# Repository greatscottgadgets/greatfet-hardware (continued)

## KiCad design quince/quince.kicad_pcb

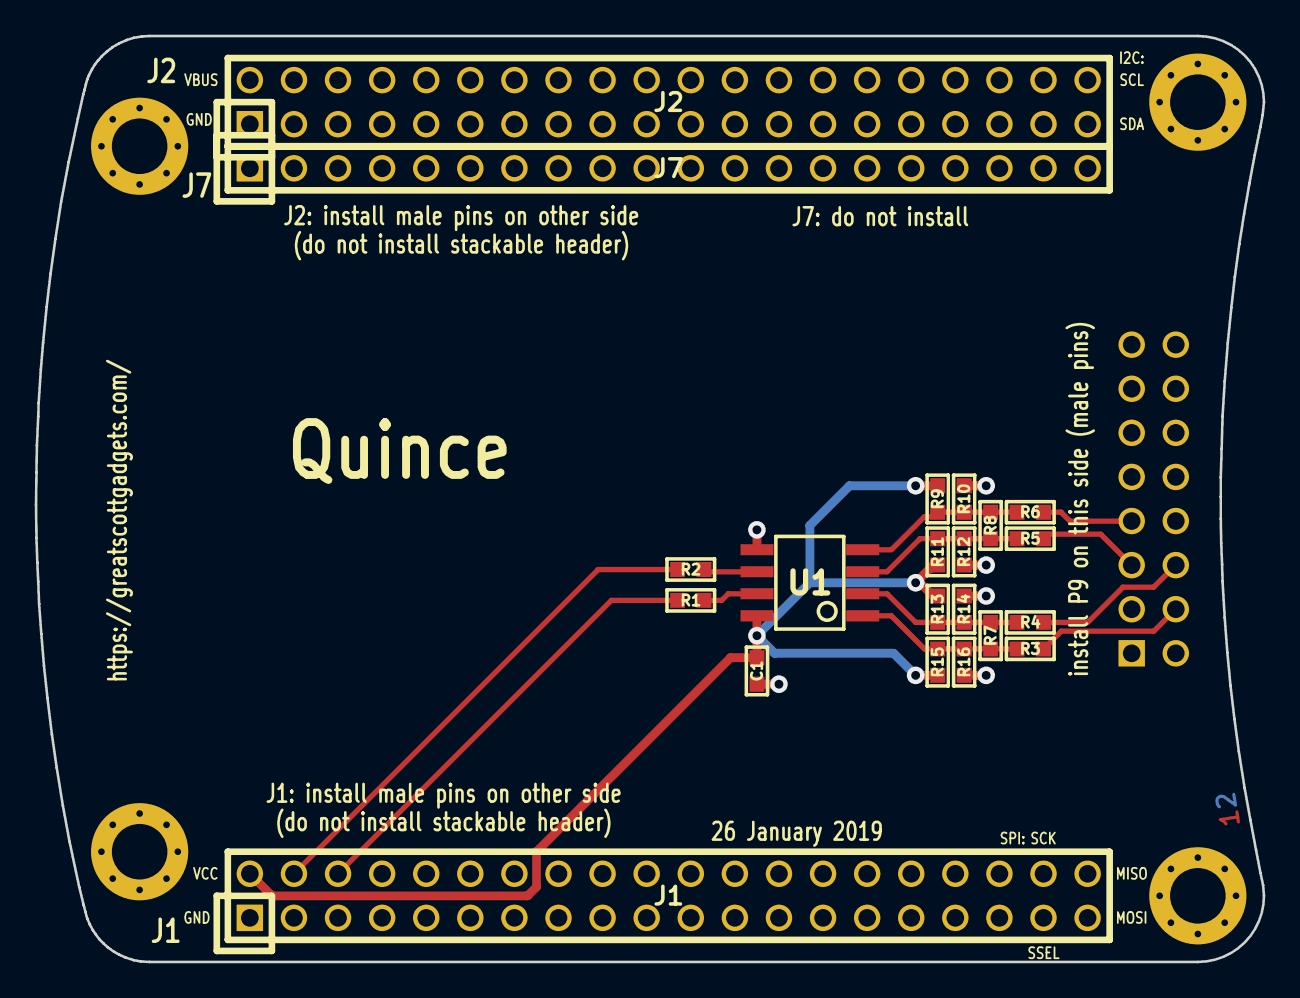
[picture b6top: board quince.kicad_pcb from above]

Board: 2 copper layers, 70.7 x 53.3 mm, 26 parts (1 on the bottom side), 14 nets.

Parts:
C1: C; 0603
J1: NEIGHBOR1; HEADER-2x20
J2: NEIGHBOR2; HEADER-2x20
J7: BONUS_ROW; HEADER-1x20
MH1, MH2, MH3, MH4: MOUNTING_HOLE; HOLE126MIL-COPPER
P9: BASEBAND; HEADER-2x8
R1, R2, R3, R4, R5, R6: 0; 0603
R7, R8, R9, R10, R11, R12, R13, R14, R15, R16: R; 0603
U1: TLV3502; SOIC8-154

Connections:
/+IN_A: R3.1, R7.1, R15.2, R16.1, U1.1
/+IN_B: R5.1, R8.1, R11.2, R12.1, U1.3
/-IN_A: R4.1, R7.2, R13.2, R14.1, U1.2
/-IN_B: R6.1, R8.2, R9.2, R10.1, U1.4
/OUT_A: R1.2, U1.7
/OUT_B: R2.2, U1.6
/P0_0: J1.4, R2.1
/P0_1: J1.6, R1.1
/RXBBI+: P9.7, R6.2
/RXBBI-: P9.5, R5.2
/RXBBQ+: P9.6, R4.2
/RXBBQ-: P9.4, R3.2
GND: C1.1, J1.1, J2.1, J7.1, J7.10, J7.19, MH1.1, MH2.1, MH3.1, MH4.1, P9.1, P9.2, P9.3, P9.8, P9.9, P9.14, P9.15, P9.16, R10.2, R12.2, R14.2, R16.2, U1.5
VCC: C1.2, J1.2, R9.1, R11.1, R13.1, R15.1, U1.8

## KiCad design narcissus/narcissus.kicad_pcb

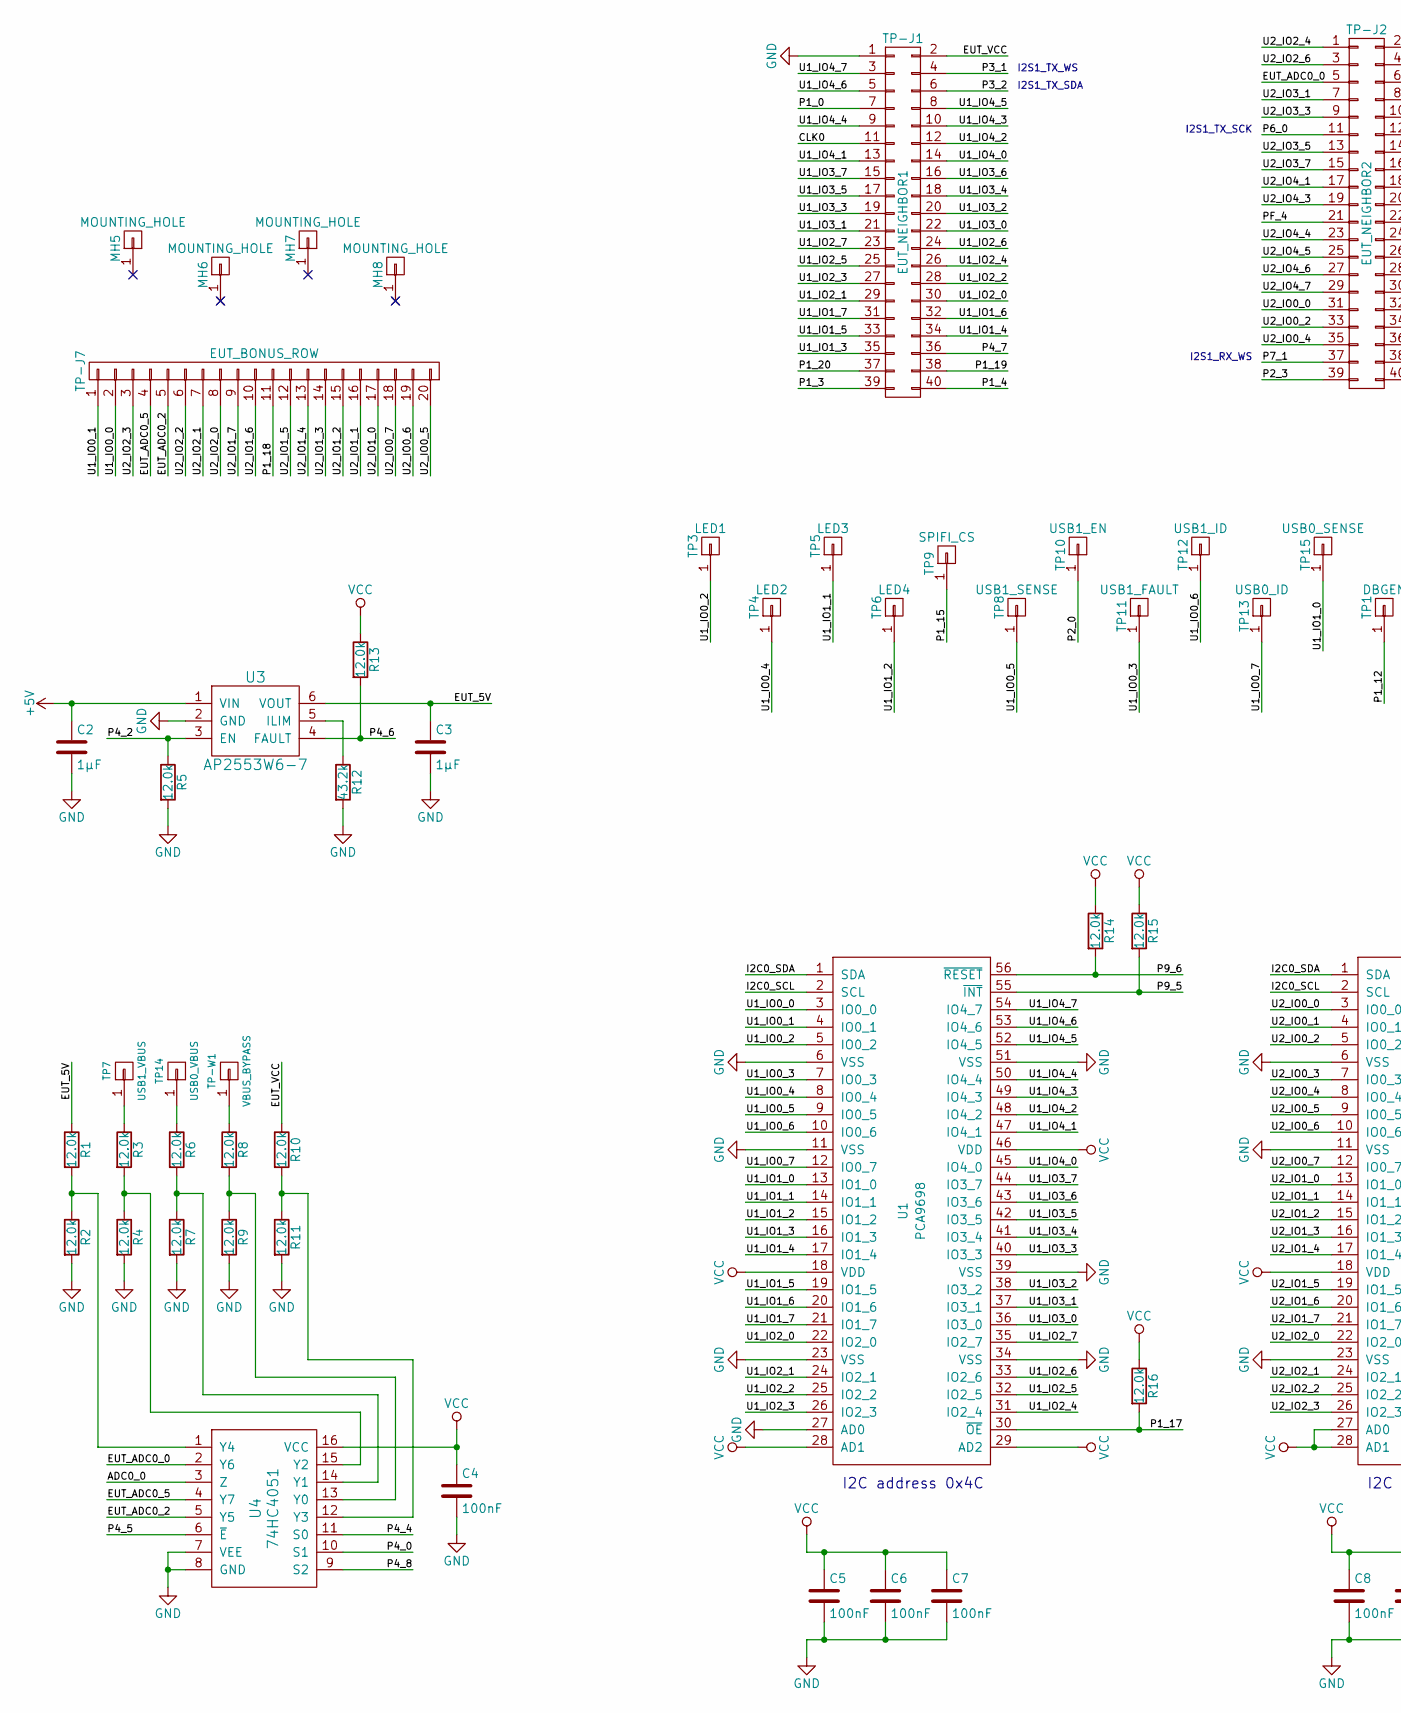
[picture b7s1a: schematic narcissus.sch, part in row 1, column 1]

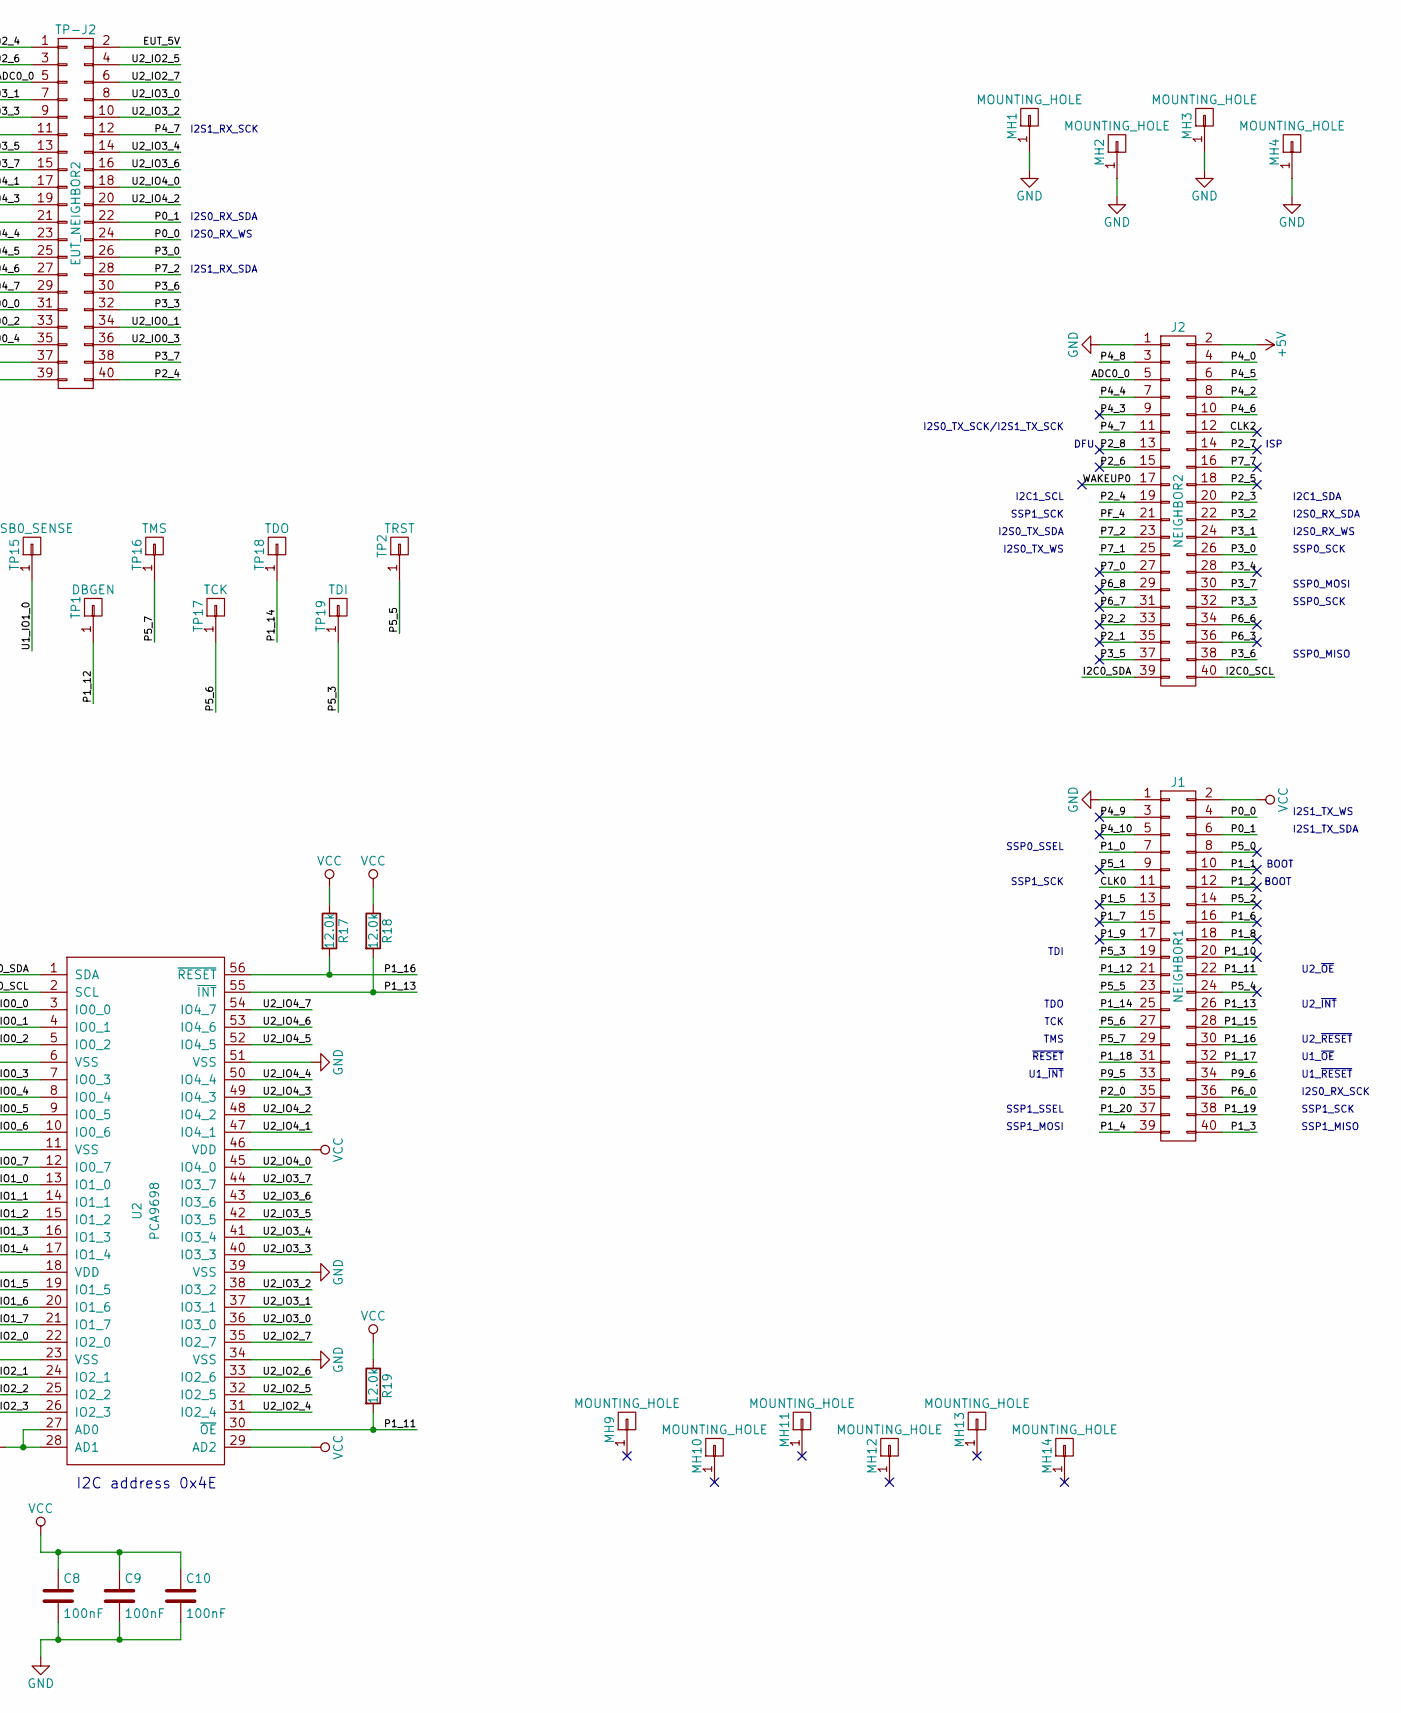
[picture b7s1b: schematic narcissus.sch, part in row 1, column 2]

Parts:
C2, C3: 1µF; 0603; Part Number CL10A105KP8NNNC
C4, C5, C6, C7, C8, C9, C10: 100nF; 0603; Part Number C0603C104M4RAC
J1: NEIGHBOR1; HEADER-2x20-REVERSE; Part Number SSW-120-01-F-D
J2: NEIGHBOR2; HEADER-2x20-REVERSE; Part Number SSW-120-01-F-D
MH1, MH2, MH3, MH4, MH5, MH6, MH7, MH8, MH9, MH10, MH11, MH12, MH13, MH14: MOUNTING_HOLE; HOLE126MIL-COPPER
R1, R2, R3, R4, R5, R6, R7, R8, R9, R10, R11, R13, R14, R15, R16, R17, R18, R19: 12.0k; 0603; Part Number RMCF0603FT12K0
R12: 43.2k; 0603; Part Number RC0603FR-0743K2L
TP1: DBGEN; HEADER-1x1-TESTPROBE
TP2: TRST; HEADER-1x1-TESTPROBE
TP3: LED1; HEADER-1x1-TESTPROBE
TP4: LED2; HEADER-1x1-TESTPROBE
TP5: LED3; HEADER-1x1-TESTPROBE
TP6: LED4; HEADER-1x1-TESTPROBE
TP7: USB1_VBUS; HEADER-1x1-TESTPROBE
TP8: USB1_SENSE; HEADER-1x1-TESTPROBE
TP9: SPIFI_CS; HEADER-1x1-TESTPROBE
TP10: USB1_EN; HEADER-1x1-TESTPROBE
TP11: USB1_FAULT; HEADER-1x1-TESTPROBE
TP12: USB1_ID; HEADER-1x1-TESTPROBE
TP13: USB0_ID; HEADER-1x1-TESTPROBE
TP14: USB0_VBUS; HEADER-1x1-TESTPROBE
TP15: USB0_SENSE; HEADER-1x1-TESTPROBE
TP16: TMS; HEADER-1x1-TESTPROBE
TP17: TCK; HEADER-1x1-TESTPROBE
TP18: TDO; HEADER-1x1-TESTPROBE
TP19: TDI; HEADER-1x1-TESTPROBE
TP-J1: EUT_NEIGHBOR1; HEADER-2x20-TESTPROBE; Part Number SSW-120-01-F-D
TP-J2: EUT_NEIGHBOR2; HEADER-2x20-TESTPROBE; Part Number SSW-120-01-F-D
TP-J7: EUT_BONUS_ROW; HEADER-1x20-TESTPROBE; Part Number PRPC020SAAN-RC
TP-W1: VBUS_BYPASS; HEADER-1x1-TESTPROBE
U1, U2: PCA9698; TSSOP56; Part Number PCA9698DGG,512
U3: AP2553W6-7; SOT457; Part Number AP2553W6-7
U4: 74HC4051; SOIC16; Part Number 74HC4051D,653

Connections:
+5V: C2.1, J2.2, U3.1 (VIN)
/ADC0_0: J2.5, U4.3 (Z)
/CLK0: J1.11, TP-J1.11
/CLK2: J2.12
/EUT_5V: C3.1, R1.1, TP-J2.2, U3.6 (VOUT)
/EUT_ADC0_0: TP-J2.5, U4.2 (Y6)
/EUT_ADC0_2: TP-J7.5, U4.5 (Y5)
/EUT_ADC0_5: TP-J7.4, U4.4 (Y7)
/EUT_VCC: R10.1, TP-J1.2
/I2C0_SCL: J2.40, U1.2 (SCL), U2.2 (SCL)
/I2C0_SDA: J2.39, U1.1 (SDA), U2.1 (SDA)
/P0_0: J1.4, TP-J2.24
/P0_1: J1.6, TP-J2.22
/P1_0: J1.7, TP-J1.7
/P1_1: J1.10
/P1_2: J1.12
/P1_3: J1.40, TP-J1.39
/P1_4: J1.39, TP-J1.40
/P1_5: J1.13
/P1_6: J1.16
/P1_7: J1.15
/P1_8: J1.18
/P1_9: J1.17
/P1_10: J1.20
/P1_11: J1.22, R19.2, U2.30 (~OE~)
/P1_12: J1.21, TP1.1
/P1_13: J1.26, R18.2, U2.55 (~INT~)
/P1_14: J1.25, TP18.1
/P1_15: J1.28, TP9.1
/P1_16: J1.30, R17.2, U2.56 (~RESET~)
/P1_17: J1.32, R16.2, U1.30 (~OE~)
/P1_18: J1.31, TP-J7.11
/P1_19: J1.38, TP-J1.38
/P1_20: J1.37, TP-J1.37
/P2_0: J1.35, TP10.1
/P2_1: J2.35
/P2_2: J2.33
/P2_3: J2.20, TP-J2.39
/P2_4: J2.19, TP-J2.40
/P2_5: J2.18
/P2_6: J2.15
/P2_7: J2.14
/P2_8: J2.13
/P3_0: J2.26, TP-J2.26
/P3_1: J2.24, TP-J1.4
/P3_2: J2.22, TP-J1.6
/P3_3: J2.32, TP-J2.32
/P3_4: J2.28
/P3_5: J2.37
/P3_6: J2.38, TP-J2.30
/P3_7: J2.30, TP-J2.38
/P4_0: J2.4, U4.10 (S1)
/P4_2: J2.8, R5.1, U3.3 (EN)
/P4_3: J2.9
/P4_4: J2.7, U4.11 (S0)
/P4_5: J2.6, U4.6 (~E~)
/P4_6: J2.10, R13.2, U3.4 (FAULT)
/P4_7: J2.11, TP-J1.36, TP-J2.12
/P4_8: J2.3, U4.9 (S2)
/P4_9: J1.3
/P4_10: J1.5
/P5_0: J1.8
/P5_1: J1.9
/P5_2: J1.14
/P5_3: J1.19, TP19.1
/P5_4: J1.24
/P5_5: J1.23, TP2.1
/P5_6: J1.27, TP17.1
/P5_7: J1.29, TP16.1
/P6_0: J1.36, TP-J2.11
/P6_3: J2.36
/P6_6: J2.34
/P6_7: J2.31
/P6_8: J2.29
/P7_0: J2.27
/P7_1: J2.25, TP-J2.37
/P7_2: J2.23, TP-J2.28
/P7_7: J2.16
/P9_5: J1.33, R15.2, U1.55 (~INT~)
/P9_6: J1.34, R14.2, U1.56 (~RESET~)
/PF_4: J2.21, TP-J2.21
/U1_IO0_0: TP-J7.2, U1.3 (IO0_0)
/U1_IO0_1: TP-J7.1, U1.4 (IO0_1)
/U1_IO0_2: TP3.1, U1.5 (IO0_2)
/U1_IO0_3: TP11.1, U1.7 (IO0_3)
/U1_IO0_4: TP4.1, U1.8 (IO0_4)
/U1_IO0_5: TP8.1, U1.9 (IO0_5)
/U1_IO0_6: TP12.1, U1.10 (IO0_6)
/U1_IO0_7: TP13.1, U1.12 (IO0_7)
/U1_IO1_0: TP15.1, U1.13 (IO1_0)
/U1_IO1_1: TP5.1, U1.14 (IO1_1)
/U1_IO1_2: TP6.1, U1.15 (IO1_2)
/U1_IO1_3: TP-J1.35, U1.16 (IO1_3)
/U1_IO1_4: TP-J1.34, U1.17 (IO1_4)
/U1_IO1_5: TP-J1.33, U1.19 (IO1_5)
/U1_IO1_6: TP-J1.32, U1.20 (IO1_6)
/U1_IO1_7: TP-J1.31, U1.21 (IO1_7)
/U1_IO2_0: TP-J1.30, U1.22 (IO2_0)
/U1_IO2_1: TP-J1.29, U1.24 (IO2_1)
/U1_IO2_2: TP-J1.28, U1.25 (IO2_2)
/U1_IO2_3: TP-J1.27, U1.26 (IO2_3)
/U1_IO2_4: TP-J1.26, U1.31 (IO2_4)
/U1_IO2_5: TP-J1.25, U1.32 (IO2_5)
/U1_IO2_6: TP-J1.24, U1.33 (IO2_6)
/U1_IO2_7: TP-J1.23, U1.35 (IO2_7)
/U1_IO3_0: TP-J1.22, U1.36 (IO3_0)
/U1_IO3_1: TP-J1.21, U1.37 (IO3_1)
/U1_IO3_2: TP-J1.20, U1.38 (IO3_2)
/U1_IO3_3: TP-J1.19, U1.40 (IO3_3)
/U1_IO3_4: TP-J1.18, U1.41 (IO3_4)
/U1_IO3_5: TP-J1.17, U1.42 (IO3_5)
/U1_IO3_6: TP-J1.16, U1.43 (IO3_6)
/U1_IO3_7: TP-J1.15, U1.44 (IO3_7)
/U1_IO4_0: TP-J1.14, U1.45 (IO4_0)
/U1_IO4_1: TP-J1.13, U1.47 (IO4_1)
/U1_IO4_2: TP-J1.12, U1.48 (IO4_2)
/U1_IO4_3: TP-J1.10, U1.49 (IO4_3)
/U1_IO4_4: TP-J1.9, U1.50 (IO4_4)
/U1_IO4_5: TP-J1.8, U1.52 (IO4_5)
/U1_IO4_6: TP-J1.5, U1.53 (IO4_6)
/U1_IO4_7: TP-J1.3, U1.54 (IO4_7)
/U2_IO0_0: TP-J2.31, U2.3 (IO0_0)
/U2_IO0_1: TP-J2.34, U2.4 (IO0_1)
/U2_IO0_2: TP-J2.33, U2.5 (IO0_2)
/U2_IO0_3: TP-J2.36, U2.7 (IO0_3)
/U2_IO0_4: TP-J2.35, U2.8 (IO0_4)
/U2_IO0_5: TP-J7.20, U2.9 (IO0_5)
/U2_IO0_6: TP-J7.19, U2.10 (IO0_6)
/U2_IO0_7: TP-J7.18, U2.12 (IO0_7)
/U2_IO1_0: TP-J7.17, U2.13 (IO1_0)
/U2_IO1_1: TP-J7.16, U2.14 (IO1_1)
/U2_IO1_2: TP-J7.15, U2.15 (IO1_2)
/U2_IO1_3: TP-J7.14, U2.16 (IO1_3)
/U2_IO1_4: TP-J7.13, U2.17 (IO1_4)
/U2_IO1_5: TP-J7.12, U2.19 (IO1_5)
/U2_IO1_6: TP-J7.10, U2.20 (IO1_6)
/U2_IO1_7: TP-J7.9, U2.21 (IO1_7)
/U2_IO2_0: TP-J7.8, U2.22 (IO2_0)
/U2_IO2_1: TP-J7.7, U2.24 (IO2_1)
/U2_IO2_2: TP-J7.6, U2.25 (IO2_2)
/U2_IO2_3: TP-J7.3, U2.26 (IO2_3)
/U2_IO2_4: TP-J2.1, U2.31 (IO2_4)
/U2_IO2_5: TP-J2.4, U2.32 (IO2_5)
/U2_IO2_6: TP-J2.3, U2.33 (IO2_6)
/U2_IO2_7: TP-J2.6, U2.35 (IO2_7)
/U2_IO3_0: TP-J2.8, U2.36 (IO3_0)
/U2_IO3_1: TP-J2.7, U2.37 (IO3_1)
/U2_IO3_2: TP-J2.10, U2.38 (IO3_2)
/U2_IO3_3: TP-J2.9, U2.40 (IO3_3)
/U2_IO3_4: TP-J2.14, U2.41 (IO3_4)
/U2_IO3_5: TP-J2.13, U2.42 (IO3_5)
/U2_IO3_6: TP-J2.16, U2.43 (IO3_6)
/U2_IO3_7: TP-J2.15, U2.44 (IO3_7)
/U2_IO4_0: TP-J2.18, U2.45 (IO4_0)
/U2_IO4_1: TP-J2.17, U2.47 (IO4_1)
/U2_IO4_2: TP-J2.20, U2.48 (IO4_2)
/U2_IO4_3: TP-J2.19, U2.49 (IO4_3)
/U2_IO4_4: TP-J2.23, U2.50 (IO4_4)
/U2_IO4_5: TP-J2.25, U2.52 (IO4_5)
/U2_IO4_6: TP-J2.27, U2.53 (IO4_6)
/U2_IO4_7: TP-J2.29, U2.54 (IO4_7)
/WAKEUP0: J2.17
GND: C2.2, C3.2, C4.2, C5.2, C6.2, C7.2, C8.2, C9.2, C10.2, J1.1, J2.1, MH1.1, MH2.1, MH3.1, MH4.1, R2.2, R4.2, R5.2, R7.2, R9.2, R11.2, R12.2, TP-J1.1, U1.6 (VSS), U1.11 (VSS), U1.23 (VSS), U1.27 (AD0), U1.34 (VSS), U1.39 (VSS), U1.51 (VSS), U2.6 (VSS), U2.11 (VSS), U2.23 (VSS), U2.34 (VSS), U2.39 (VSS), U2.51 (VSS), U3.2 (GND), U4.7 (VEE), U4.8 (GND)
unnamed: R1.2, R2.1, U4.1 (Y4)
unnamed: R3.1, TP7.1
unnamed: R3.2, R4.1, U4.15 (Y2)
unnamed: R6.1, TP14.1
unnamed: R6.2, R7.1, U4.14 (Y1)
unnamed: R8.1, TP-W1.1
unnamed: R8.2, R9.1, U4.13 (Y0)
unnamed: R10.2, R11.1, U4.12 (Y3)
unnamed: R12.1, U3.5 (ILIM)
VCC: C4.1, C5.1, C6.1, C7.1, C8.1, C9.1, C10.1, J1.2, R13.1, R14.1, R15.1, R16.1, R17.1, R18.1, R19.1, U1.18 (VDD), U1.28 (AD1), U1.29 (AD2), U1.46 (VDD), U2.18 (VDD), U2.27 (AD0), U2.28 (AD1), U2.29 (AD2), U2.46 (VDD), U4.16 (VCC)

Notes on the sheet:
ISP
DFU
BOOT
I2C address 0x4C
I2C address 0x4E
SSP1_SCK
SSP0_SCK
SSP0_SSEL
SSP0_MOSI
SSP0_MISO
SSP1_MISO
SSP1_SSEL
SSP1_MOSI
I2S1_RX_SCK
I2S1_RX_SDA
I2S0_TX_SDA
I2S0_TX_SCK/I2S1_TX_SCK
I2S1_RX_WS
I2S0_TX_WS
I2S1_TX_SDA
I2S0_RX_SDA
I2S1_TX_WS
I2S0_RX_WS
I2S0_RX_SCK
I2S1_TX_SCK
I2C1_SCL
I2C1_SDA
~RESET~
TDO
TMS
TCK
TDI
U1_~RESET~
U1_~INT~
U1_~OE~
U2_~INT~
U2_~RESET~
U2_~OE~

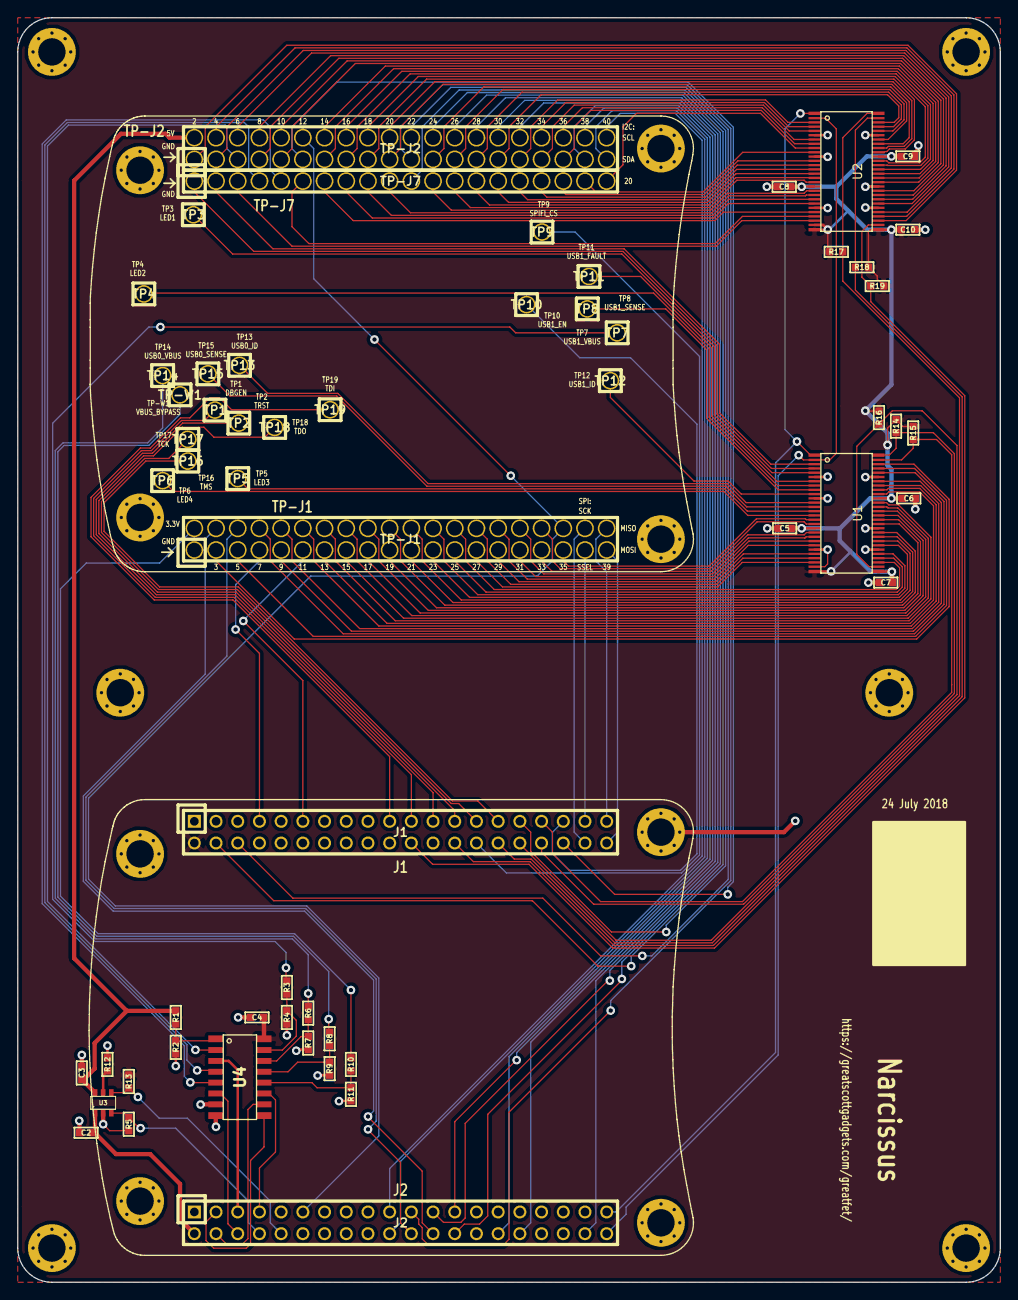
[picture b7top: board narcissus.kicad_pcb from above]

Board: 2 copper layers, 115.0 x 148.0 mm, 71 parts (0 on the bottom side), 142 nets.

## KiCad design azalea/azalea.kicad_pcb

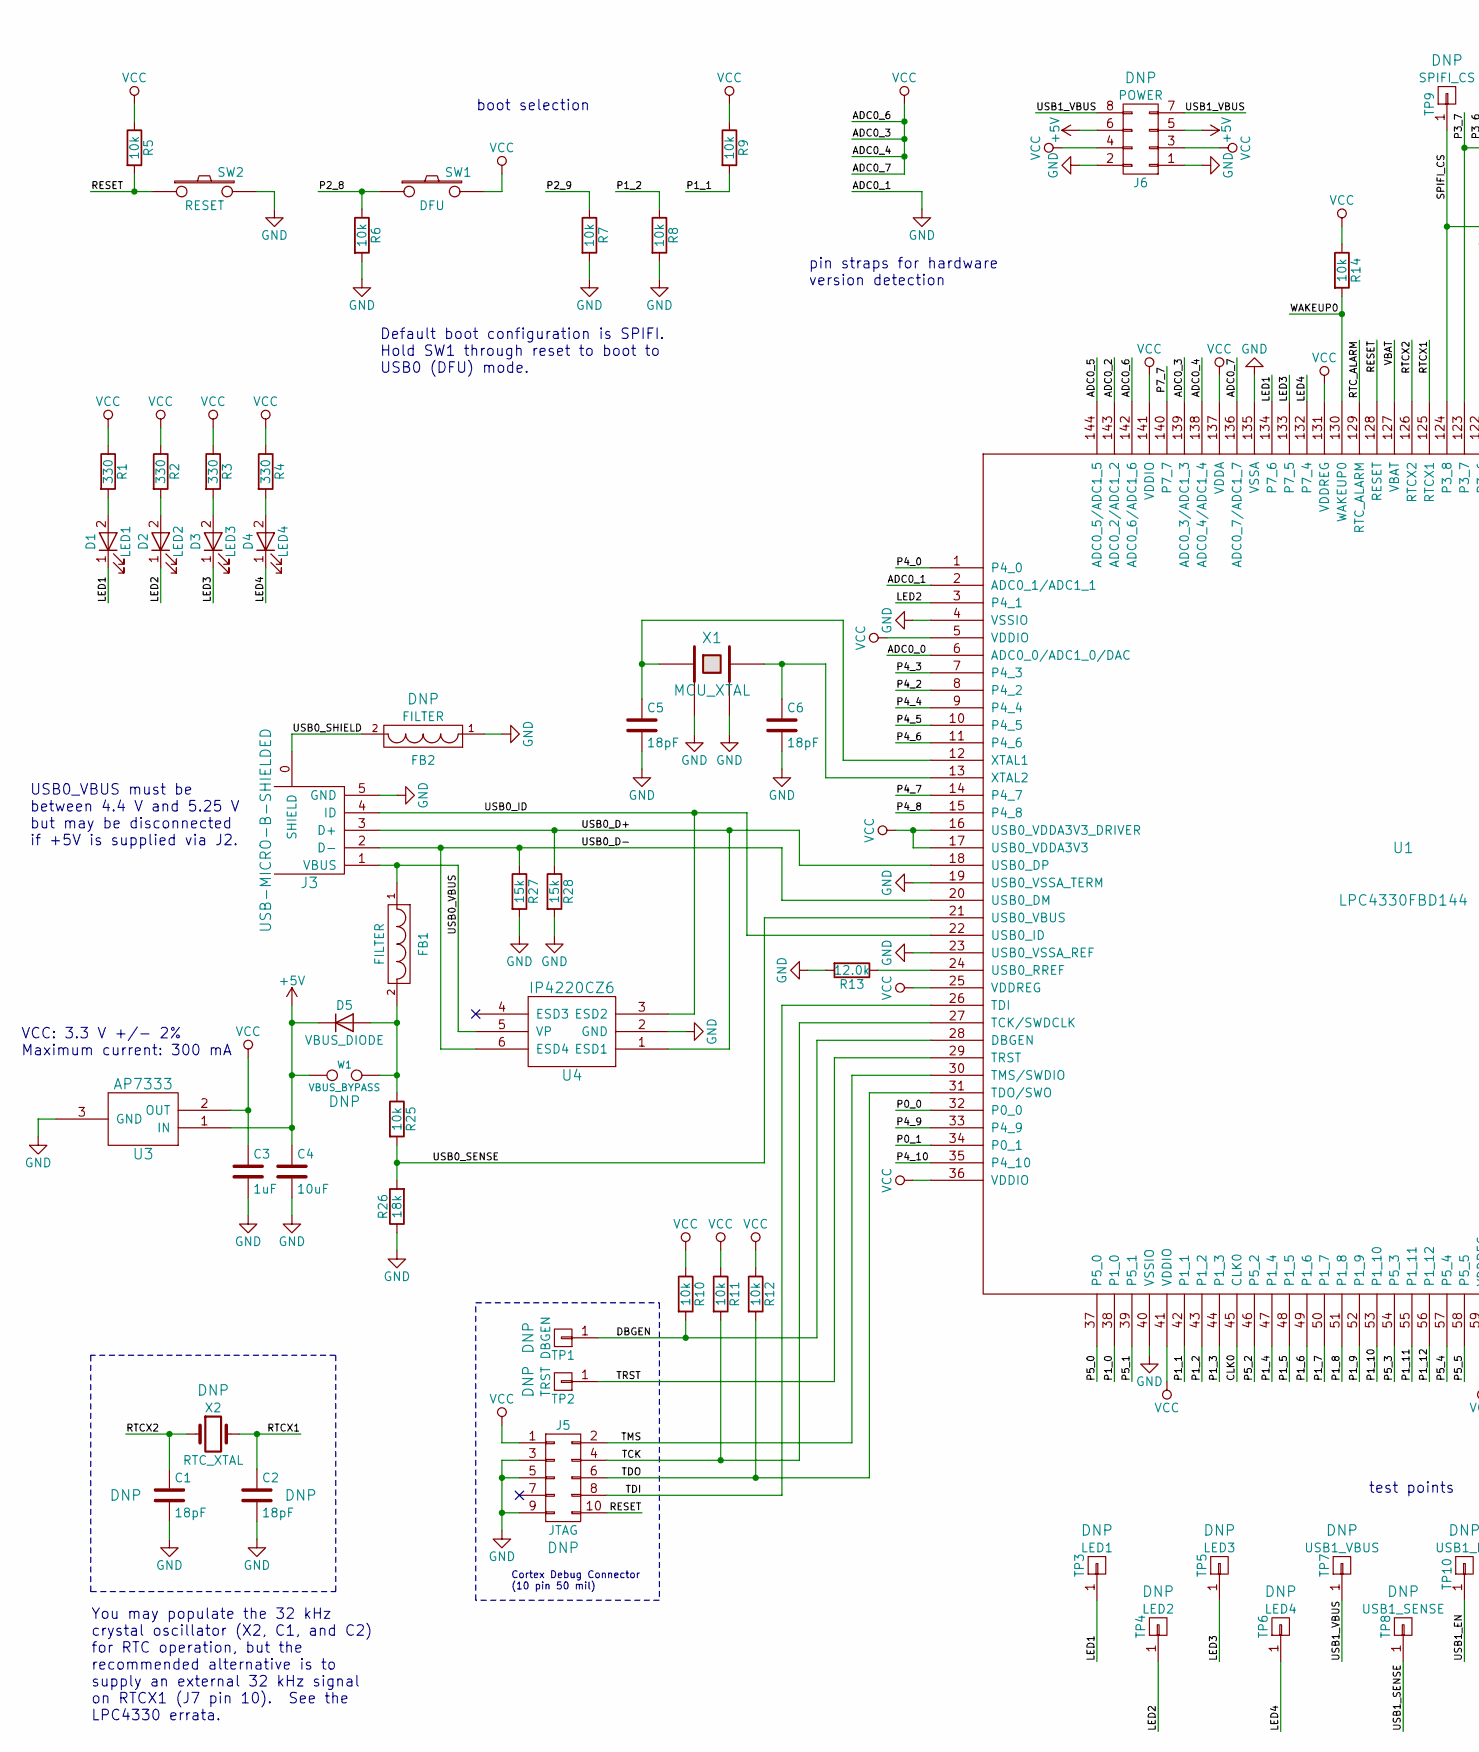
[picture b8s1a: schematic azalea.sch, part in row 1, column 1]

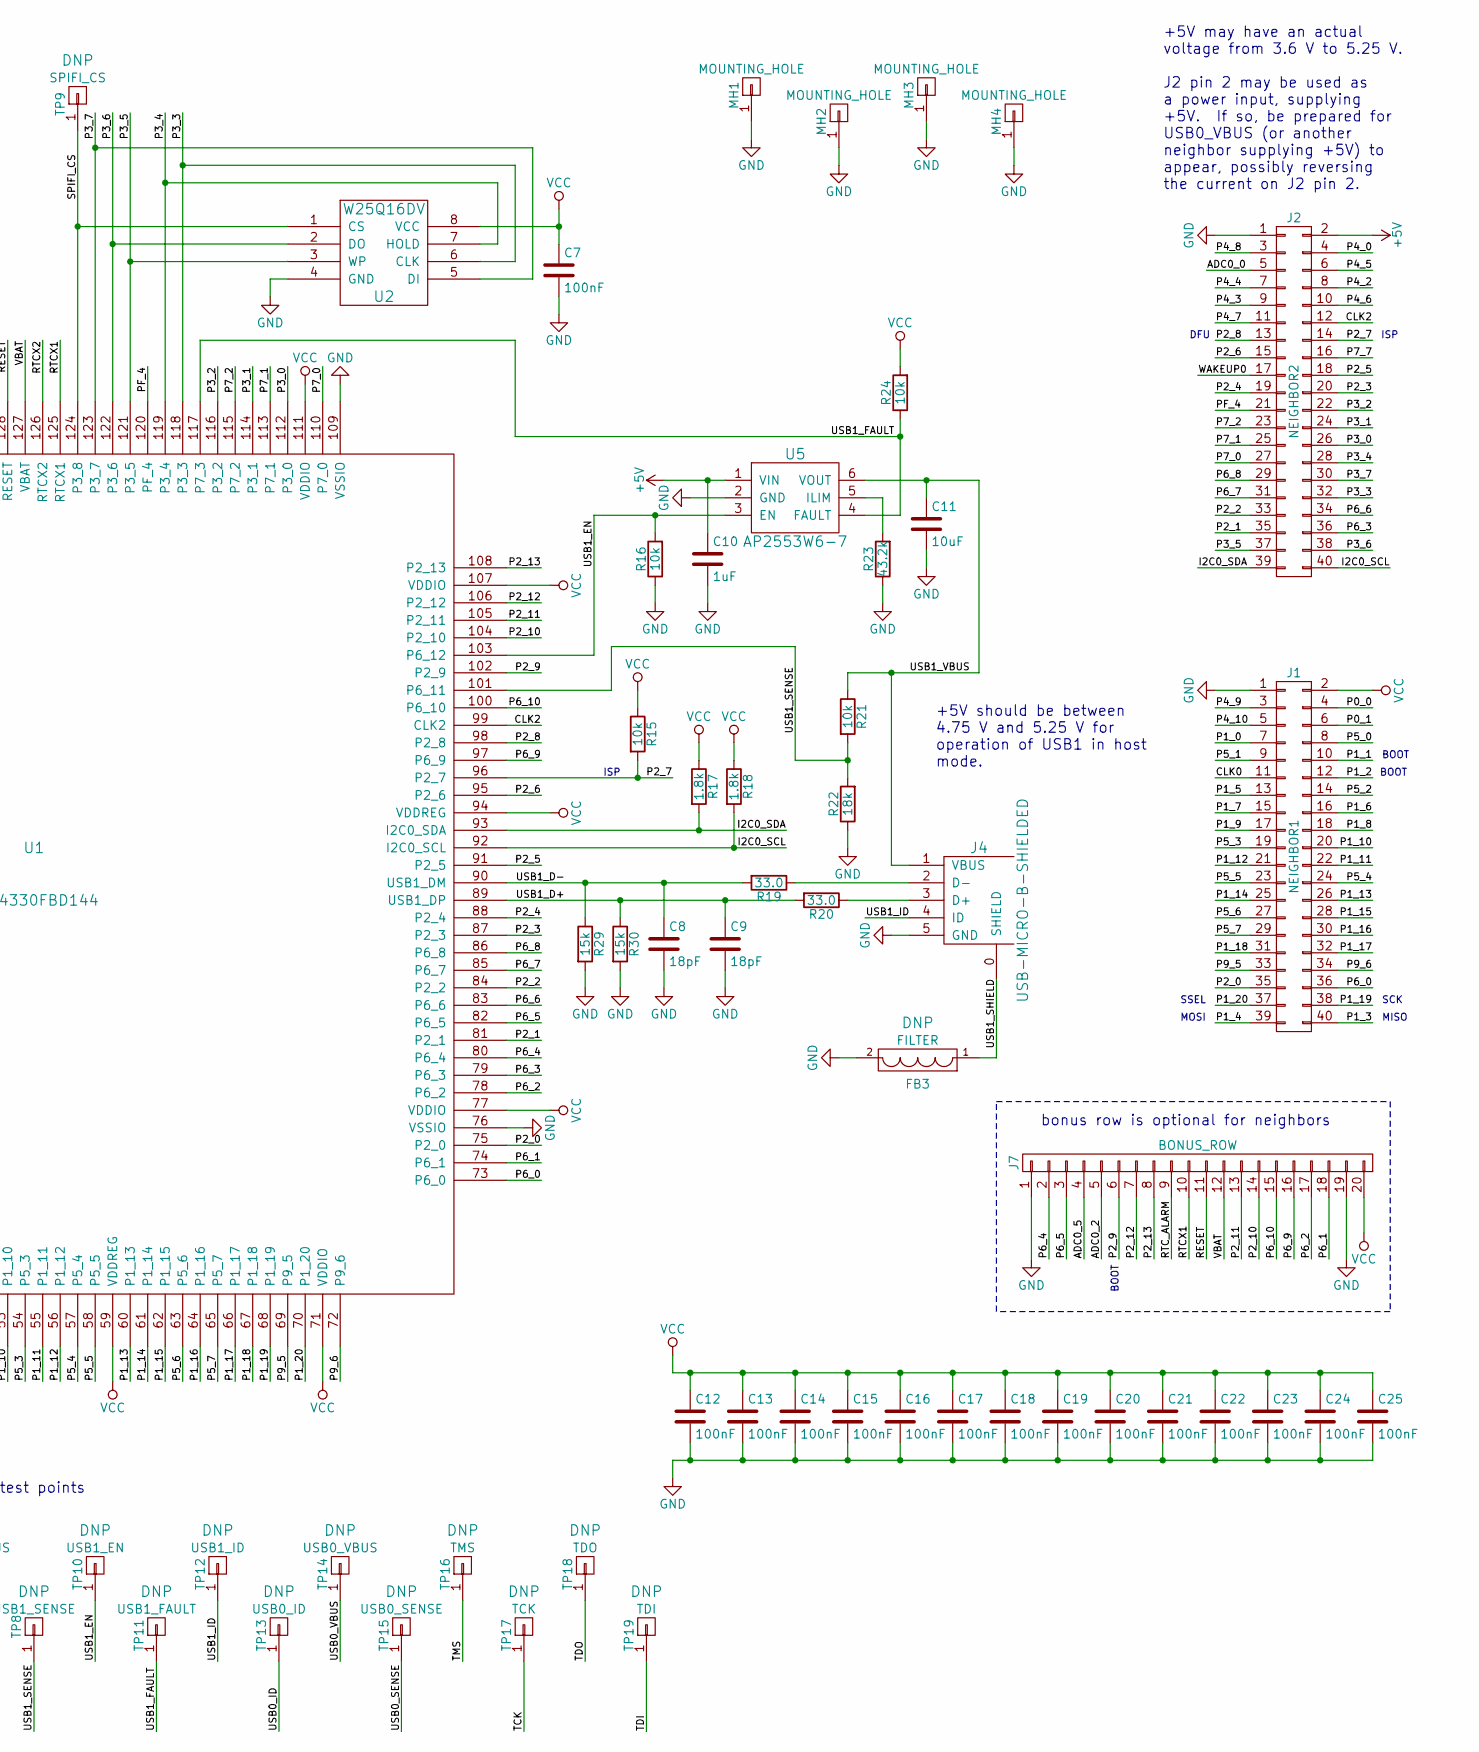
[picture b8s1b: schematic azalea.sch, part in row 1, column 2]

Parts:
C1, C2, C5, C6, C8, C9: 18pF; 0603; Part Number C0603C180J5GAC
C3, C10: 1uF; 0603; Part Number LMK107B7105KA-T
C4, C11: 10uF; 0805; Part Number LMK212ABJ106KG-T
C7, C12, C13, C14, C15, C16, C17, C18, C19, C20, C21, C22, C23, C24, C25: 100nF; 0603; Part Number C0603C104M4RAC
D1: LED1; 0603D; Part Number SML-LX0603GW-TR
D2: LED2; 0603D; Part Number SML-LX0603YW-TR
D3: LED3; 0603D; Part Number SML-LX0603GW-TR
D4: LED4; 0603D; Part Number SML-LX0603YW-TR
D5: VBUS_DIODE; SOD128; Part Number PMEG3050EP,115
FB1, FB2, FB3: FILTER; 0805; Part Number BLM21PG221SN1D
J1: NEIGHBOR1; HEADER-2x20; Part Number SSW-120-01-F-D
J2: NEIGHBOR2; HEADER-2x20; Part Number SSW-120-01-F-D
J3, J4: USB-MICRO-B-SHIELDED; USB-MICROB-FCI-10103592-LONGPADS; Part Number 10103592-0001LF
J5: JTAG; 50MIL-HEADER-2x5-TH
J6: POWER; HEADER-SMT-2x4
J7: BONUS_ROW; HEADER-1x20; Part Number PRPC020SAAN-RC
MH1, MH2, MH3, MH4: MOUNTING_HOLE; HOLE126MIL-COPPER
R1, R2, R3, R4: 330; 0603; Part Number RMCF0603JT330R
R5, R6, R7, R8, R9, R10, R11, R12, R14, R15, R16, R21, R24, R25: 10k; 0603; Part Number ERJ-3GEYJ103V
R13: 12.0k; 0603; Part Number RMCF0603FT12K0
R17, R18: 1.8k; 0603; Part Number RMCF0603JT1K80
R19, R20: 33.0; 0603; Part Number RC0603FR-0733RL
R22, R26: 18k; 0603; Part Number RC0603JR-0718KL
R23: 43.2k; 0603; Part Number RC0603FR-0743K2L
R27, R28, R29, R30: 15k; 0603; Part Number RC0603JR-0715KL
SW1: DFU; SWITCH-PTS840-P; Part Number PTS840 PM SMTR LFS
SW2: RESET; SWITCH-PTS840-P; Part Number PTS840 PM SMTR LFS
TP1: DBGEN; TESTPOINT-50MIL
TP2: TRST; TESTPOINT-50MIL
TP3: LED1; TESTPOINT-50MIL
TP4: LED2; TESTPOINT-50MIL
TP5: LED3; TESTPOINT-50MIL
TP6: LED4; TESTPOINT-50MIL
TP7: USB1_VBUS; TESTPOINT-50MIL
TP8: USB1_SENSE; TESTPOINT-50MIL
TP9: SPIFI_CS; TESTPOINT-50MIL
TP10: USB1_EN; TESTPOINT-50MIL
TP11: USB1_FAULT; TESTPOINT-50MIL
TP12: USB1_ID; TESTPOINT-50MIL
TP13: USB0_ID; TESTPOINT-50MIL
TP14: USB0_VBUS; TESTPOINT-50MIL
TP15: USB0_SENSE; TESTPOINT-50MIL
TP16: TMS; TESTPOINT-50MIL
TP17: TCK; TESTPOINT-50MIL
TP18: TDO; TESTPOINT-50MIL
TP19: TDI; TESTPOINT-50MIL
U1: LPC4330FBD144; LQFP144; Part Number LPC4330FBD144,551
U2: W25Q16DV; SOIC8-208; Part Number W25Q16JVSSIQ
U3: AP7333; SOT23-3; Part Number AP7333-33SAG-7
U4: IP4220CZ6; SOT457; Part Number IP4220CZ6,125
U5: AP2553W6-7; SOT457; Part Number AP2553W6-7
W1: VBUS_BYPASS; 0603-JUMPER
X1: MCU_XTAL; XTAL3.2x2.5mm-EXT; Part Number 7V-12.000MAAE-T
X2: RTC_XTAL; XTAL-AB26TRQ; Part Number AB26TRQ-32.768KHZ-T

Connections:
+5V: C4.1, C10.1, D5.1 (K), J2.2, J6.5, J6.6, U3.1 (IN), U5.1 (VIN), W1.1
/ADC0_0: J2.5, U1.6 (ADC0_0/ADC1_0/DAC)
/ADC0_2: J7.5, U1.143 (ADC0_2/ADC1_2)
/ADC0_5: J7.4, U1.144 (ADC0_5/ADC1_5)
/CLK0: J1.11, U1.45 (CLK0)
/CLK2: J2.12, U1.99 (CLK2)
/DBGEN: R10.2, TP1.1, U1.28 (DBGEN)
/I2C0_SCL: J2.40, R18.2, U1.92 (I2C0_SCL)
/I2C0_SDA: J2.39, R17.2, U1.93 (I2C0_SDA)
/LED1: D1.1 (K), TP3.1, U1.134 (P7_6)
/LED2: D2.1 (K), TP4.1, U1.3 (P4_1)
/LED3: D3.1 (K), TP5.1, U1.133 (P7_5)
/LED4: D4.1 (K), TP6.1, U1.132 (P7_4)
/P0_0: J1.4, U1.32 (P0_0)
/P0_1: J1.6, U1.34 (P0_1)
/P1_0: J1.7, U1.38 (P1_0)
/P1_1: J1.10, R9.2, U1.42 (P1_1)
/P1_2: J1.12, R8.1, U1.43 (P1_2)
/P1_3: J1.40, U1.44 (P1_3)
/P1_4: J1.39, U1.47 (P1_4)
/P1_5: J1.13, U1.48 (P1_5)
/P1_6: J1.16, U1.49 (P1_6)
/P1_7: J1.15, U1.50 (P1_7)
/P1_8: J1.18, U1.51 (P1_8)
/P1_9: J1.17, U1.52 (P1_9)
/P1_10: J1.20, U1.53 (P1_10)
/P1_11: J1.22, U1.55 (P1_11)
/P1_12: J1.21, U1.56 (P1_12)
/P1_13: J1.26, U1.60 (P1_13)
/P1_14: J1.25, U1.61 (P1_14)
/P1_15: J1.28, U1.62 (P1_15)
/P1_16: J1.30, U1.64 (P1_16)
/P1_17: J1.32, U1.66 (P1_17)
/P1_18: J1.31, U1.67 (P1_18)
/P1_19: J1.38, U1.68 (P1_19)
/P1_20: J1.37, U1.70 (P1_20)
/P2_0: J1.35, U1.75 (P2_0)
/P2_1: J2.35, U1.81 (P2_1)
/P2_2: J2.33, U1.84 (P2_2)
/P2_3: J2.20, U1.87 (P2_3)
/P2_4: J2.19, U1.88 (P2_4)
/P2_5: J2.18, U1.91 (P2_5)
/P2_6: J2.15, U1.95 (P2_6)
/P2_7: J2.14, R15.2, U1.96 (P2_7)
/P2_8: J2.13, R6.1, SW1.1, U1.98 (P2_8)
/P2_9: J7.6, R7.1, U1.102 (P2_9)
/P2_10: J7.14, U1.104 (P2_10)
/P2_11: J7.13, U1.105 (P2_11)
/P2_12: J7.7, U1.106 (P2_12)
/P2_13: J7.8, U1.108 (P2_13)
/P3_0: J2.26, U1.112 (P3_0)
/P3_1: J2.24, U1.114 (P3_1)
/P3_2: J2.22, U1.116 (P3_2)
/P3_3: J2.32, U1.118 (P3_3), U2.6 (CLK)
/P3_4: J2.28, U1.119 (P3_4), U2.7 (HOLD)
/P3_5: J2.37, U1.121 (P3_5), U2.3 (WP)
/P3_6: J2.38, U1.122 (P3_6), U2.2 (DO)
/P3_7: J2.30, U1.123 (P3_7), U2.5 (DI)
/P4_0: J2.4, U1.1 (P4_0)
/P4_2: J2.8, U1.8 (P4_2)
/P4_3: J2.9, U1.7 (P4_3)
/P4_4: J2.7, U1.9 (P4_4)
/P4_5: J2.6, U1.10 (P4_5)
/P4_6: J2.10, U1.11 (P4_6)
/P4_7: J2.11, U1.14 (P4_7)
/P4_8: J2.3, U1.15 (P4_8)
/P4_9: J1.3, U1.33 (P4_9)
/P4_10: J1.5, U1.35 (P4_10)
/P5_0: J1.8, U1.37 (P5_0)
/P5_1: J1.9, U1.39 (P5_1)
/P5_2: J1.14, U1.46 (P5_2)
/P5_3: J1.19, U1.54 (P5_3)
/P5_4: J1.24, U1.57 (P5_4)
/P5_5: J1.23, U1.58 (P5_5)
/P5_6: J1.27, U1.63 (P5_6)
/P5_7: J1.29, U1.65 (P5_7)
/P6_0: J1.36, U1.73 (P6_0)
/P6_1: J7.18, U1.74 (P6_1)
/P6_2: J7.17, U1.78 (P6_2)
/P6_3: J2.36, U1.79 (P6_3)
/P6_4: J7.2, U1.80 (P6_4)
/P6_5: J7.3, U1.82 (P6_5)
/P6_6: J2.34, U1.83 (P6_6)
/P6_7: J2.31, U1.85 (P6_7)
/P6_8: J2.29, U1.86 (P6_8)
/P6_9: J7.16, U1.97 (P6_9)
/P6_10: J7.15, U1.100 (P6_10)
/P7_0: J2.27, U1.110 (P7_0)
/P7_1: J2.25, U1.113 (P7_1)
/P7_2: J2.23, U1.115 (P7_2)
/P7_7: J2.16, U1.140 (P7_7)
/P9_5: J1.33, U1.69 (P9_5)
/P9_6: J1.34, U1.72 (P9_6)
/PF_4: J2.21, U1.120 (PF_4)
/RESET: J5.10, J7.11, R5.2, SW2.1, U1.128 (RESET)
/RTCX1: C2.1, J7.10, U1.125 (RTCX1), X2.2
/RTCX2: C1.1, U1.126 (RTCX2), X2.1
/RTC_ALARM: J7.9, U1.129 (RTC_ALARM)
/SPIFI_CS: TP9.1, U1.124 (P3_8), U2.1 (CS)
/TCK: J5.4, R11.2, TP17.1, U1.27 (TCK/SWDCLK)
/TDI: J5.8, TP19.1, U1.26 (TDI)
/TDO: J5.6, R12.2, TP18.1, U1.31 (TDO/SWO)
/TMS: J5.2, TP16.1, U1.30 (TMS/SWDIO)
/TRST: TP2.1, U1.29 (TRST)
/USB0_D+: J3.3 (D+), R28.1, U1.18 (USB0_DP), U4.1 (ESD1)
/USB0_D-: J3.2 (D-), R27.1, U1.20 (USB0_DM), U4.6 (ESD4)
/USB0_ID: J3.4 (ID), TP13.1, U1.22 (USB0_ID), U4.3 (ESD2)
/USB0_SENSE: R25.2, R26.2, TP15.1, U1.21 (USB0_VBUS)
/USB0_SHIELD: FB2.2, J3.0 (SHIELD)
/USB0_VBUS: FB1.1, J3.1 (VBUS), TP14.1, U4.5 (VP)
/USB1_D+: C9.1, R20.2, R30.1, U1.89 (USB1_DP)
/USB1_D-: C8.1, R19.2, R29.1, U1.90 (USB1_DM)
/USB1_EN: R16.2, TP10.1, U1.103 (P6_12), U5.3 (EN)
/USB1_FAULT: R24.1, TP11.1, U1.117 (P7_3), U5.4 (FAULT)
/USB1_ID: J4.4 (ID), TP12.1
/USB1_SENSE: R21.2, R22.2, TP8.1, U1.101 (P6_11)
/USB1_SHIELD: FB3.1, J4.0 (SHIELD)
/USB1_VBUS: C11.1, J4.1 (VBUS), J6.7, J6.8, R21.1, TP7.1, U5.6 (VOUT)
/VBAT: J7.12, U1.127 (VBAT)
/WAKEUP0: J2.17, R14.2, U1.130 (WAKEUP0)
GND: C1.2, C2.2, C3.2, C4.2, C5.2, C6.2, C7.2, C8.2, C9.2, C10.2, C11.2, C12.2, C13.2, C14.2, C15.2, C16.2, C17.2, C18.2, C19.2, C20.2, C21.2, C22.2, C23.2, C24.2, C25.2, FB2.1, FB3.2, J1.1, J2.1, J3.5 (GND), J4.5 (GND), J5.3, J5.5, J5.9, J6.1, J6.2, J7.1, J7.19, MH1.1, MH2.1, MH3.1, MH4.1, R6.2, R7.2, R8.2, R13.2, R16.1, R22.1, R23.1, R26.1, R27.2, R28.2, R29.2, R30.2, SW2.2, U1.2 (ADC0_1/ADC1_1), U1.4 (VSSIO), U1.19 (USB0_VSSA_TERM), U1.23 (USB0_VSSA_REF), U1.40 (VSSIO), U1.76 (VSSIO), U1.109 (VSSIO), U1.135 (VSSA), U2.4 (GND), U3.3 (GND), U4.2 (GND), U5.2 (GND), X1.2, X1.4
unnamed: C5.1, U1.12 (XTAL1), X1.1
unnamed: C6.1, U1.13 (XTAL2), X1.3
unnamed: D1.2 (A), R1.2
unnamed: D2.2 (A), R2.2
unnamed: D3.2 (A), R3.2
unnamed: D4.2 (A), R4.2
unnamed: D5.2 (A), FB1.2, R25.1, W1.2
unnamed: J4.2 (D-), R19.1
unnamed: J4.3 (D+), R20.1
unnamed: R13.1, U1.24 (USB0_RREF)
unnamed: R23.2, U5.5 (ILIM)
VCC: C3.1, C7.1, C12.1, C13.1, C14.1, C15.1, C16.1, C17.1, C18.1, C19.1, C20.1, C21.1, C22.1, C23.1, C24.1, C25.1, J1.2, J5.1, J6.3, J6.4, J7.20, R1.1, R2.1, R3.1, R4.1, R5.1, R9.1, R10.1, R11.1, R12.1, R14.1, R15.1, R17.1, R18.1, R24.2, SW1.2, U1.5 (VDDIO), U1.16 (USB0_VDDA3V3_DRIVER), U1.17 (USB0_VDDA3V3), U1.25 (VDDREG), U1.36 (VDDIO), U1.41 (VDDIO), U1.59 (VDDREG), U1.71 (VDDIO), U1.77 (VDDIO), U1.94 (VDDREG), U1.107 (VDDIO), U1.111 (VDDIO), U1.131 (VDDREG), U1.136 (ADC0_7/ADC1_7), U1.137 (VDDA), U1.138 (ADC0_4/ADC1_4), U1.139 (ADC0_3/ADC1_3), U1.141 (VDDIO), U1.142 (ADC0_6/ADC1_6), U2.8 (VCC), U3.2 (OUT)

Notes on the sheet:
MISO
MOSI
SCK
SSEL
ISP
DFU
BOOT
bonus row is optional for neighbors
boot selection
test points
Default boot configuration is SPIFI. Hold SW1 through reset to boot to USB0 (DFU) mode.
Cortex Debug Connector (10 pin 50 mil)
VCC: 3.3 V +/- 2% Maximum current: 300 mA
USB0_VBUS must be between 4.4 V and 5.25 V but may be disconnected if +5V is supplied via J2.
+5V may have an actual voltage from 3.6 V to 5.25 V. J2 pin 2 may be used as a power input, supplying +5V. If so, be prepared for USB0_VBUS (or another neighbor supplying +5V) to appear, possibly reversing the current on J2 pin 2.
+5V should be between 4.75 V and 5.25 V for operation of USB1 in host mode.
pin straps for hardware version detection
You may populate the 32 kHz crystal oscillator (X2, C1, and C2) for RTC operation, but the recommended alternative is to supply an external 32 kHz signal on RTCX1 (J7 pin 10). See the LPC4330 errata.
